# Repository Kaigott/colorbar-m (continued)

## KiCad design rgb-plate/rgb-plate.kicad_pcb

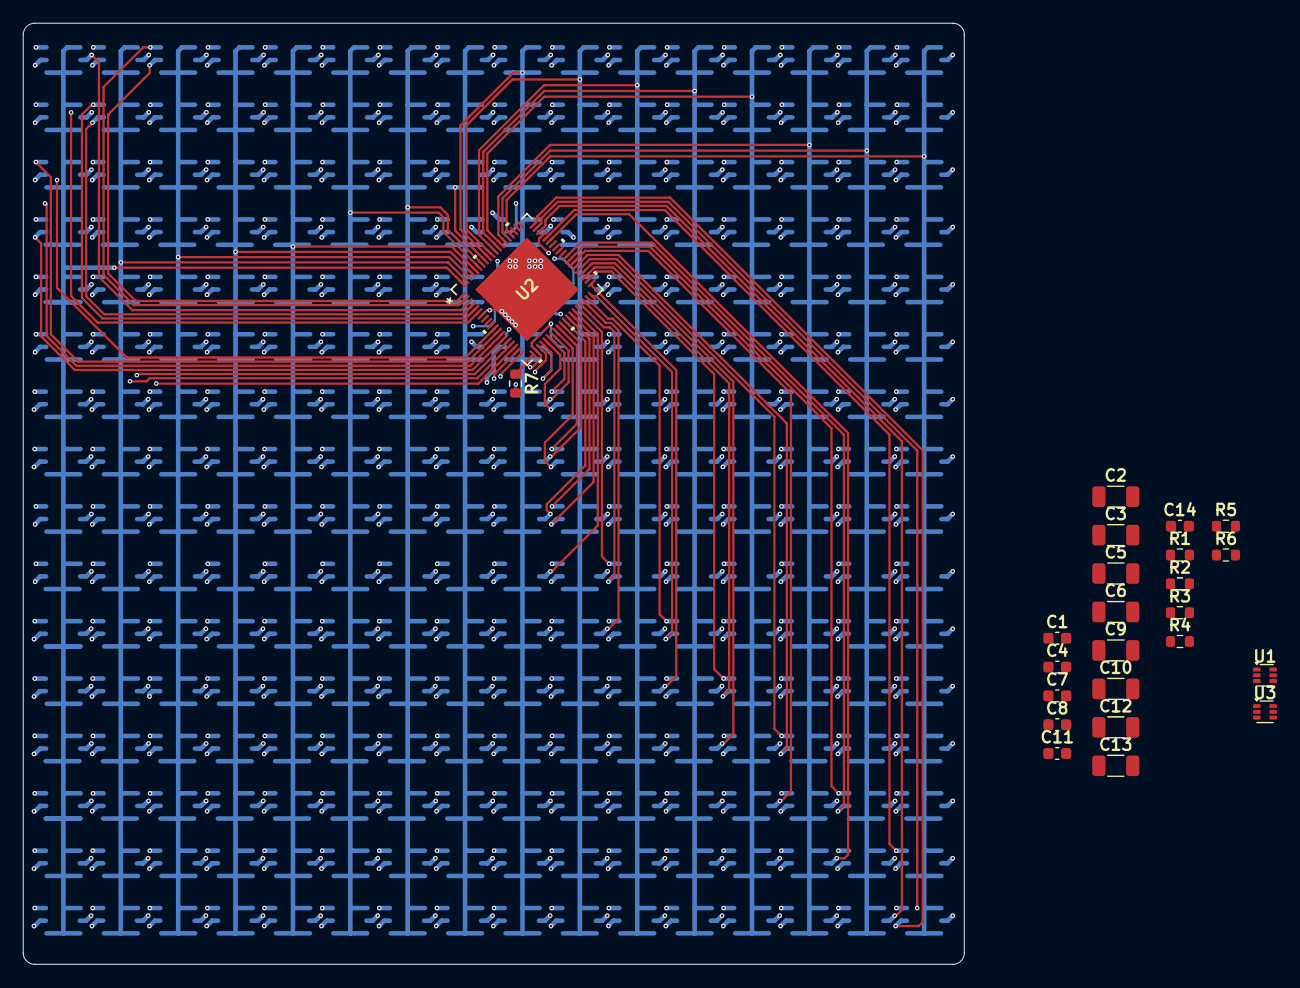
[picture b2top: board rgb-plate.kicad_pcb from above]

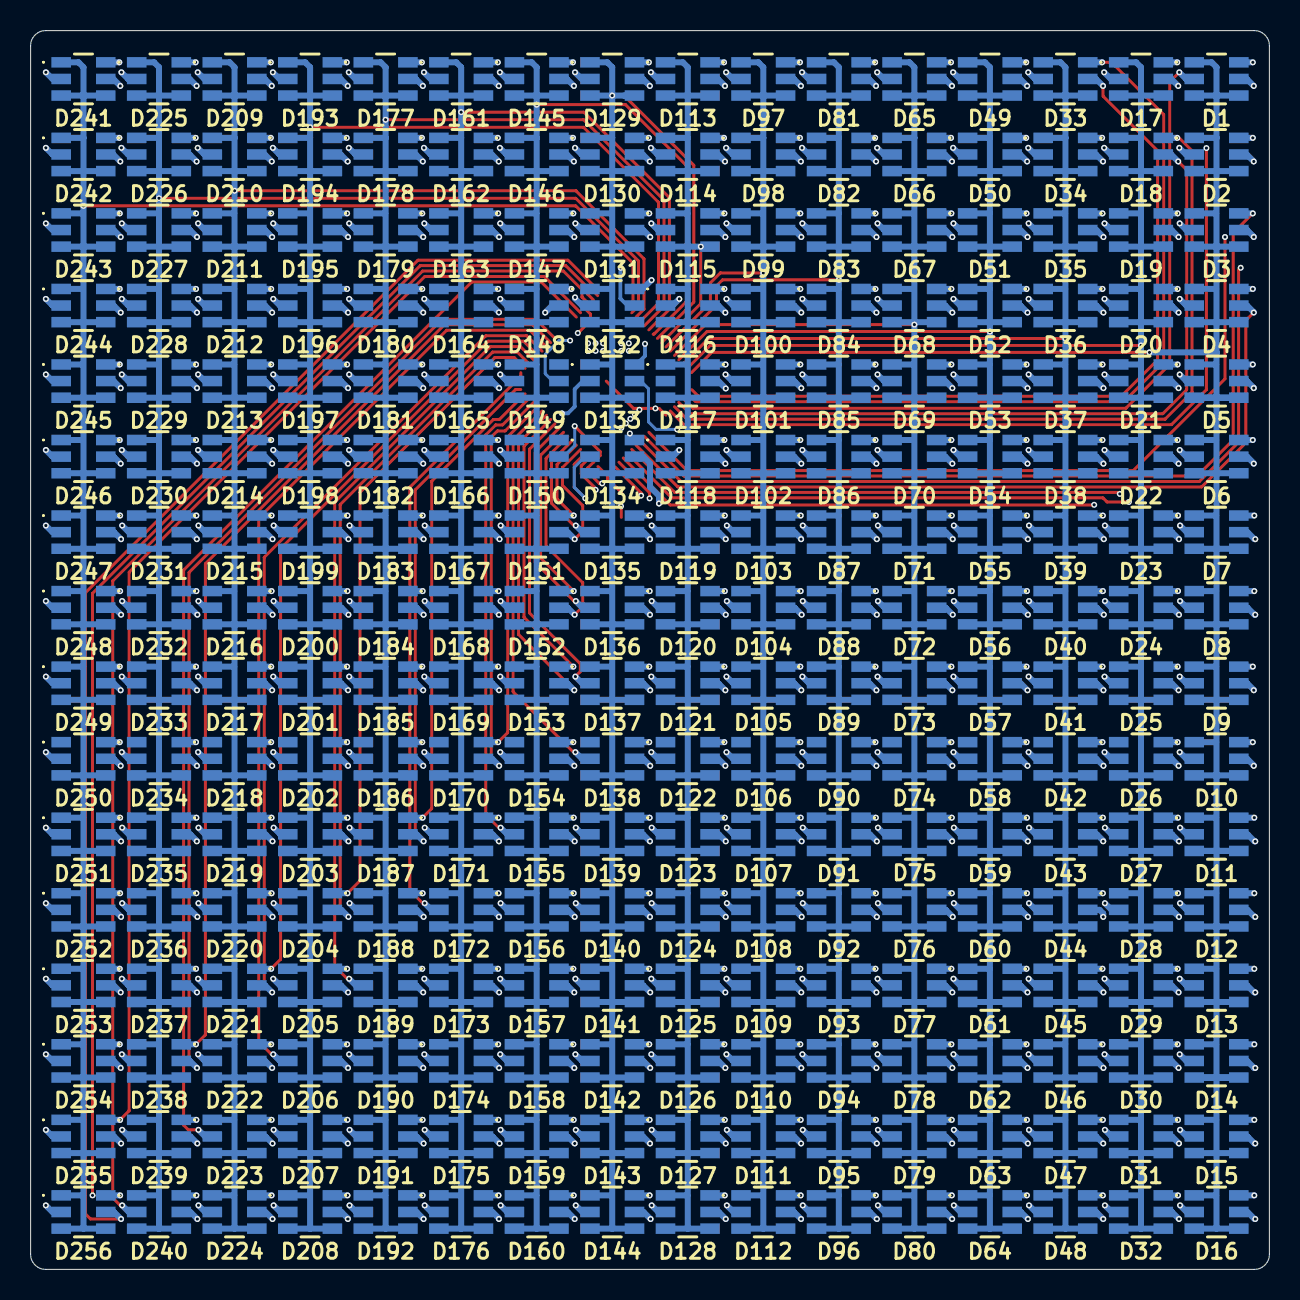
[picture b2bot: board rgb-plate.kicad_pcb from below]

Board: 4 copper layers, 82.0 x 82.0 mm, 280 parts (256 on the bottom side), 77 nets.

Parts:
C1, C4, C8, C11: 0.1uF; C_0603_1608Metric
C2, C3, C9, C10: 10uF; C_1206_3216Metric
C5, C6, C12, C13: 22uF; C_1206_3216Metric
C7, C14: 10nF; C_0603_1608Metric
D1, D2, D3, D4, D5, D6, D7, D8, D9, D10, D11, D12, D13, D14, D15, D16, D17, D18, D19, D20, D21, D22, D23, D24, D25, D26, D27, D28, D29, D30, D31, D32, D33, D34, D35, D36, D37, D38, D39, D40, D41, D42, D43, D44, D45, D46, D47, D48, D49, D50, D51, D52, D53, D54, D55, D56, D57, D58, D59, D60, D61, D62, D63, D64, D65, D66, D67, D68, D69, D70, D71, D72, D73, D74, D75, D76, D77, D78, D79, D80, D81, D82, D83, D84, D85, D86, D87, D88, D89, D90, D91, D92, D93, D94, D95, D96, D97, D98, D99, D100, D101, D102, D103, D104, D105, D106, D107, D108, D109, D110, D111, D112, D113, D114, D115, D116, D117, D118, D119, D120, D121, D122, D123, D124, D125, D126, D127, D128, D129, D130, D131, D132, D133, D134, D135, D136, D137, D138, D139, D140, D141, D142, D143, D144, D145, D146, D147, D148, D149, D150, D151, D152, D153, D154, D155, D156, D157, D158, D159, D160, D161, D162, D163, D164, D165, D166, D167, D168, D169, D170, D171, D172, D173, D174, D175, D176, D177, D178, D179, D180, D181, D182, D183, D184, D185, D186, D187, D188, D189, D190, D191, D192, D193, D194, D195, D196, D197, D198, D199, D200, D201, D202, D203, D204, D205, D206, D207, D208, D209, D210, D211, D212, D213, D214, D215, D216, D217, D218, D219, D220, D221, D222, D223, D224, D225, D226, D227, D228, D229, D230, D231, D232, D233, D234, D235, D236, D237, D238, D239, D240, D241, D242, D243, D244, D245, D246, D247, D248, D249, D250, D251, D252, D253, D254, D255, D256: LED_RGB; LRTBGVSR4U4VJW8A8BD83S4U7Z
R1, R3, R4, R6: 10k; R_0603_1608Metric
R2: 37.4k; R_0603_1608Metric
R5: 26.1k; R_0603_1608Metric
R7: R; R_0603_1608Metric
U1, U3: TPS562202; SOT-563
U2: LP5891MRRFR; VQFN76_RRF_TEX

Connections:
+2V8: C12.2, C13.2, R5.1, U2.9 (VR), U2.10 (VR)
+3V8: C5.2, C6.2, R2.1, U2.48 (VB), U2.49 (VB), U2.50 (VG), U2.51 (VG)
+12V: C2.1, C3.1, C4.1, C9.1, C10.1, C11.1, U1.1 (VIN), U3.1 (VIN)
/B0: D1.A3 (BA), D17.A3 (BA), D33.A3 (BA), D49.A3 (BA), D65.A3 (BA), D81.A3 (BA), D97.A3 (BA), D113.A3 (BA), D129.A3 (BA), D145.A3 (BA), D161.A3 (BA), D177.A3 (BA), D193.A3 (BA), D209.A3 (BA), D225.A3 (BA), D241.A3 (BA), U2.3 (B0)
/B1: D2.A3 (BA), D18.A3 (BA), D34.A3 (BA), D50.A3 (BA), D66.A3 (BA), D82.A3 (BA), D98.A3 (BA), D114.A3 (BA), D130.A3 (BA), D146.A3 (BA), D162.A3 (BA), D178.A3 (BA), D194.A3 (BA), D210.A3 (BA), D226.A3 (BA), D242.A3 (BA), U2.6 (B1)
/B2: D3.A3 (BA), D19.A3 (BA), D35.A3 (BA), D51.A3 (BA), D67.A3 (BA), D83.A3 (BA), D99.A3 (BA), D115.A3 (BA), D131.A3 (BA), D147.A3 (BA), D163.A3 (BA), D179.A3 (BA), D195.A3 (BA), D211.A3 (BA), D227.A3 (BA), D243.A3 (BA), U2.13 (B2)
/B3: D4.A3 (BA), D20.A3 (BA), D36.A3 (BA), D52.A3 (BA), D68.A3 (BA), D84.A3 (BA), D100.A3 (BA), D116.A3 (BA), D132.A3 (BA), D148.A3 (BA), D164.A3 (BA), D180.A3 (BA), D196.A3 (BA), D212.A3 (BA), D228.A3 (BA), D244.A3 (BA), U2.16 (B3)
/B4: D5.A3 (BA), D21.A3 (BA), D37.A3 (BA), D53.A3 (BA), D69.A3 (BA), D85.A3 (BA), D101.A3 (BA), D117.A3 (BA), D133.A3 (BA), D149.A3 (BA), D165.A3 (BA), D181.A3 (BA), D197.A3 (BA), D213.A3 (BA), D229.A3 (BA), D245.A3 (BA), U2.19 (B4)
/B5: D6.A3 (BA), D22.A3 (BA), D38.A3 (BA), D54.A3 (BA), D70.A3 (BA), D86.A3 (BA), D102.A3 (BA), D118.A3 (BA), D134.A3 (BA), D150.A3 (BA), D166.A3 (BA), D182.A3 (BA), D198.A3 (BA), D214.A3 (BA), D230.A3 (BA), D246.A3 (BA), U2.23 (B5)
/B6: D7.A3 (BA), D23.A3 (BA), D39.A3 (BA), D55.A3 (BA), D71.A3 (BA), D87.A3 (BA), D103.A3 (BA), D119.A3 (BA), D135.A3 (BA), D151.A3 (BA), D167.A3 (BA), D183.A3 (BA), D199.A3 (BA), D215.A3 (BA), D231.A3 (BA), D247.A3 (BA), U2.26 (B6)
/B7: D8.A3 (BA), D24.A3 (BA), D40.A3 (BA), D56.A3 (BA), D72.A3 (BA), D88.A3 (BA), D104.A3 (BA), D120.A3 (BA), D136.A3 (BA), D152.A3 (BA), D168.A3 (BA), D184.A3 (BA), D200.A3 (BA), D216.A3 (BA), D232.A3 (BA), D248.A3 (BA), U2.29 (B7)
/B8: D9.A3 (BA), D25.A3 (BA), D41.A3 (BA), D57.A3 (BA), D73.A3 (BA), D89.A3 (BA), D105.A3 (BA), D121.A3 (BA), D137.A3 (BA), D153.A3 (BA), D169.A3 (BA), D185.A3 (BA), D201.A3 (BA), D217.A3 (BA), D233.A3 (BA), D249.A3 (BA), U2.30 (B8)
/B9: D10.A3 (BA), D26.A3 (BA), D42.A3 (BA), D58.A3 (BA), D74.A3 (BA), D90.A3 (BA), D106.A3 (BA), D122.A3 (BA), D138.A3 (BA), D154.A3 (BA), D170.A3 (BA), D186.A3 (BA), D202.A3 (BA), D218.A3 (BA), D234.A3 (BA), D250.A3 (BA), U2.33 (B9)
/B10: D11.A3 (BA), D27.A3 (BA), D43.A3 (BA), D59.A3 (BA), D75.A3 (BA), D91.A3 (BA), D107.A3 (BA), D123.A3 (BA), D139.A3 (BA), D155.A3 (BA), D171.A3 (BA), D187.A3 (BA), D203.A3 (BA), D219.A3 (BA), D235.A3 (BA), D251.A3 (BA), U2.36 (B10)
/B11: D12.A3 (BA), D28.A3 (BA), D44.A3 (BA), D60.A3 (BA), D76.A3 (BA), D92.A3 (BA), D108.A3 (BA), D124.A3 (BA), D140.A3 (BA), D156.A3 (BA), D172.A3 (BA), D188.A3 (BA), D204.A3 (BA), D220.A3 (BA), D236.A3 (BA), D252.A3 (BA), U2.39 (B11)
/B12: D13.A3 (BA), D29.A3 (BA), D45.A3 (BA), D61.A3 (BA), D77.A3 (BA), D93.A3 (BA), D109.A3 (BA), D125.A3 (BA), D141.A3 (BA), D157.A3 (BA), D173.A3 (BA), D189.A3 (BA), D205.A3 (BA), D221.A3 (BA), D237.A3 (BA), D253.A3 (BA), U2.42 (B12)
/B13: D14.A3 (BA), D30.A3 (BA), D46.A3 (BA), D62.A3 (BA), D78.A3 (BA), D94.A3 (BA), D110.A3 (BA), D126.A3 (BA), D142.A3 (BA), D158.A3 (BA), D174.A3 (BA), D190.A3 (BA), D206.A3 (BA), D222.A3 (BA), D238.A3 (BA), D254.A3 (BA), U2.45 (B13)
/B14: D15.A3 (BA), D31.A3 (BA), D47.A3 (BA), D63.A3 (BA), D79.A3 (BA), D95.A3 (BA), D111.A3 (BA), D127.A3 (BA), D143.A3 (BA), D159.A3 (BA), D175.A3 (BA), D191.A3 (BA), D207.A3 (BA), D223.A3 (BA), D239.A3 (BA), D255.A3 (BA), U2.52 (B14)
/B15: D16.A3 (BA), D32.A3 (BA), D48.A3 (BA), D64.A3 (BA), D80.A3 (BA), D96.A3 (BA), D112.A3 (BA), D128.A3 (BA), D144.A3 (BA), D160.A3 (BA), D176.A3 (BA), D192.A3 (BA), D208.A3 (BA), D224.A3 (BA), D240.A3 (BA), D256.A3 (BA), U2.55 (B15)
/G0: D1.A1 (GA), D17.A1 (GA), D33.A1 (GA), D49.A1 (GA), D65.A1 (GA), D81.A1 (GA), D97.A1 (GA), D113.A1 (GA), D129.A1 (GA), D145.A1 (GA), D161.A1 (GA), D177.A1 (GA), D193.A1 (GA), D209.A1 (GA), D225.A1 (GA), D241.A1 (GA), U2.2 (G0)
/G1: D2.A1 (GA), D18.A1 (GA), D34.A1 (GA), D50.A1 (GA), D66.A1 (GA), D82.A1 (GA), D98.A1 (GA), D114.A1 (GA), D130.A1 (GA), D146.A1 (GA), D162.A1 (GA), D178.A1 (GA), D194.A1 (GA), D210.A1 (GA), D226.A1 (GA), D242.A1 (GA), U2.5 (G1)
/G2: D3.A1 (GA), D19.A1 (GA), D35.A1 (GA), D51.A1 (GA), D67.A1 (GA), D83.A1 (GA), D99.A1 (GA), D115.A1 (GA), D131.A1 (GA), D147.A1 (GA), D163.A1 (GA), D179.A1 (GA), D195.A1 (GA), D211.A1 (GA), D227.A1 (GA), D243.A1 (GA), U2.12 (G2)
/G3: D4.A1 (GA), D20.A1 (GA), D36.A1 (GA), D52.A1 (GA), D68.A1 (GA), D84.A1 (GA), D100.A1 (GA), D116.A1 (GA), D132.A1 (GA), D148.A1 (GA), D164.A1 (GA), D180.A1 (GA), D196.A1 (GA), D212.A1 (GA), D228.A1 (GA), D244.A1 (GA), U2.15 (G3)
/G4: D5.A1 (GA), D21.A1 (GA), D37.A1 (GA), D53.A1 (GA), D69.A1 (GA), D85.A1 (GA), D101.A1 (GA), D117.A1 (GA), D133.A1 (GA), D149.A1 (GA), D165.A1 (GA), D181.A1 (GA), D197.A1 (GA), D213.A1 (GA), D229.A1 (GA), D245.A1 (GA), U2.18 (G4)
/G5: D6.A1 (GA), D22.A1 (GA), D38.A1 (GA), D54.A1 (GA), D70.A1 (GA), D86.A1 (GA), D102.A1 (GA), D118.A1 (GA), D134.A1 (GA), D150.A1 (GA), D166.A1 (GA), D182.A1 (GA), D198.A1 (GA), D214.A1 (GA), D230.A1 (GA), D246.A1 (GA), U2.22 (G5)
/G6: D7.A1 (GA), D23.A1 (GA), D39.A1 (GA), D55.A1 (GA), D71.A1 (GA), D87.A1 (GA), D103.A1 (GA), D119.A1 (GA), D135.A1 (GA), D151.A1 (GA), D167.A1 (GA), D183.A1 (GA), D199.A1 (GA), D215.A1 (GA), D231.A1 (GA), D247.A1 (GA), U2.25 (G6)
/G7: D8.A1 (GA), D24.A1 (GA), D40.A1 (GA), D56.A1 (GA), D72.A1 (GA), D88.A1 (GA), D104.A1 (GA), D120.A1 (GA), D136.A1 (GA), D152.A1 (GA), D168.A1 (GA), D184.A1 (GA), D200.A1 (GA), D216.A1 (GA), D232.A1 (GA), D248.A1 (GA), U2.28 (G7)
/G8: D9.A1 (GA), D25.A1 (GA), D41.A1 (GA), D57.A1 (GA), D73.A1 (GA), D89.A1 (GA), D105.A1 (GA), D121.A1 (GA), D137.A1 (GA), D153.A1 (GA), D169.A1 (GA), D185.A1 (GA), D201.A1 (GA), D217.A1 (GA), D233.A1 (GA), D249.A1 (GA), U2.31 (G8)
/G9: D10.A1 (GA), D26.A1 (GA), D42.A1 (GA), D58.A1 (GA), D74.A1 (GA), D90.A1 (GA), D106.A1 (GA), D122.A1 (GA), D138.A1 (GA), D154.A1 (GA), D170.A1 (GA), D186.A1 (GA), D202.A1 (GA), D218.A1 (GA), D234.A1 (GA), D250.A1 (GA), U2.34 (G9)
/G10: D11.A1 (GA), D27.A1 (GA), D43.A1 (GA), D59.A1 (GA), D75.A1 (GA), D91.A1 (GA), D107.A1 (GA), D123.A1 (GA), D139.A1 (GA), D155.A1 (GA), D171.A1 (GA), D187.A1 (GA), D203.A1 (GA), D219.A1 (GA), D235.A1 (GA), D251.A1 (GA), U2.37 (G10)
/G11: D12.A1 (GA), D28.A1 (GA), D44.A1 (GA), D60.A1 (GA), D76.A1 (GA), D92.A1 (GA), D108.A1 (GA), D124.A1 (GA), D140.A1 (GA), D156.A1 (GA), D172.A1 (GA), D188.A1 (GA), D204.A1 (GA), D220.A1 (GA), D236.A1 (GA), D252.A1 (GA), U2.40 (G11)
/G12: D13.A1 (GA), D29.A1 (GA), D45.A1 (GA), D61.A1 (GA), D77.A1 (GA), D93.A1 (GA), D109.A1 (GA), D125.A1 (GA), D141.A1 (GA), D157.A1 (GA), D173.A1 (GA), D189.A1 (GA), D205.A1 (GA), D221.A1 (GA), D237.A1 (GA), D253.A1 (GA), U2.43 (G12)
/G13: D14.A1 (GA), D30.A1 (GA), D46.A1 (GA), D62.A1 (GA), D78.A1 (GA), D94.A1 (GA), D110.A1 (GA), D126.A1 (GA), D142.A1 (GA), D158.A1 (GA), D174.A1 (GA), D190.A1 (GA), D206.A1 (GA), D222.A1 (GA), D238.A1 (GA), D254.A1 (GA), U2.46 (G13)
/G14: D15.A1 (GA), D31.A1 (GA), D47.A1 (GA), D63.A1 (GA), D79.A1 (GA), D95.A1 (GA), D111.A1 (GA), D127.A1 (GA), D143.A1 (GA), D159.A1 (GA), D175.A1 (GA), D191.A1 (GA), D207.A1 (GA), D223.A1 (GA), D239.A1 (GA), D255.A1 (GA), U2.53 (G14)
/G15: D16.A1 (GA), D32.A1 (GA), D48.A1 (GA), D64.A1 (GA), D80.A1 (GA), D96.A1 (GA), D112.A1 (GA), D128.A1 (GA), D144.A1 (GA), D160.A1 (GA), D176.A1 (GA), D192.A1 (GA), D208.A1 (GA), D224.A1 (GA), D240.A1 (GA), D256.A1 (GA), U2.56 (G15)
/LINE0: D1.C1 (GK), D1.C2 (RK), D1.C3 (BK), D2.C1 (GK), D2.C2 (RK), D2.C3 (BK), D3.C1 (GK), D3.C2 (RK), D3.C3 (BK), D4.C1 (GK), D4.C2 (RK), D4.C3 (BK), D5.C1 (GK), D5.C2 (RK), D5.C3 (BK), D6.C1 (GK), D6.C2 (RK), D6.C3 (BK), D7.C1 (GK), D7.C2 (RK), D7.C3 (BK), D8.C1 (GK), D8.C2 (RK), D8.C3 (BK), D9.C1 (GK), D9.C2 (RK), D9.C3 (BK), D10.C1 (GK), D10.C2 (RK), D10.C3 (BK), D11.C1 (GK), D11.C2 (RK), D11.C3 (BK), D12.C1 (GK), D12.C2 (RK), D12.C3 (BK), D13.C1 (GK), D13.C2 (RK), D13.C3 (BK), D14.C1 (GK), D14.C2 (RK), D14.C3 (BK), D15.C1 (GK), D15.C2 (RK), D15.C3 (BK), D16.C1 (GK), D16.C2 (RK), D16.C3 (BK), U2.76 (LINE0)
/LINE1: D17.C1 (GK), D17.C2 (RK), D17.C3 (BK), D18.C1 (GK), D18.C2 (RK), D18.C3 (BK), D19.C1 (GK), D19.C2 (RK), D19.C3 (BK), D20.C1 (GK), D20.C2 (RK), D20.C3 (BK), D21.C1 (GK), D21.C2 (RK), D21.C3 (BK), D22.C1 (GK), D22.C2 (RK), D22.C3 (BK), D23.C1 (GK), D23.C2 (RK), D23.C3 (BK), D24.C1 (GK), D24.C2 (RK), D24.C3 (BK), D25.C1 (GK), D25.C2 (RK), D25.C3 (BK), D26.C1 (GK), D26.C2 (RK), D26.C3 (BK), D27.C1 (GK), D27.C2 (RK), D27.C3 (BK), D28.C1 (GK), D28.C2 (RK), D28.C3 (BK), D29.C1 (GK), D29.C2 (RK), D29.C3 (BK), D30.C1 (GK), D30.C2 (RK), D30.C3 (BK), D31.C1 (GK), D31.C2 (RK), D31.C3 (BK), D32.C1 (GK), D32.C2 (RK), D32.C3 (BK), U2.75 (LINE1)
/LINE2: D33.C1 (GK), D33.C2 (RK), D33.C3 (BK), D34.C1 (GK), D34.C2 (RK), D34.C3 (BK), D35.C1 (GK), D35.C2 (RK), D35.C3 (BK), D36.C1 (GK), D36.C2 (RK), D36.C3 (BK), D37.C1 (GK), D37.C2 (RK), D37.C3 (BK), D38.C1 (GK), D38.C2 (RK), D38.C3 (BK), D39.C1 (GK), D39.C2 (RK), D39.C3 (BK), D40.C1 (GK), D40.C2 (RK), D40.C3 (BK), D41.C1 (GK), D41.C2 (RK), D41.C3 (BK), D42.C1 (GK), D42.C2 (RK), D42.C3 (BK), D43.C1 (GK), D43.C2 (RK), D43.C3 (BK), D44.C1 (GK), D44.C2 (RK), D44.C3 (BK), D45.C1 (GK), D45.C2 (RK), D45.C3 (BK), D46.C1 (GK), D46.C2 (RK), D46.C3 (BK), D47.C1 (GK), D47.C2 (RK), D47.C3 (BK), D48.C1 (GK), D48.C2 (RK), D48.C3 (BK), U2.74 (LINE2)
/LINE3: D49.C1 (GK), D49.C2 (RK), D49.C3 (BK), D50.C1 (GK), D50.C2 (RK), D50.C3 (BK), D51.C1 (GK), D51.C2 (RK), D51.C3 (BK), D52.C1 (GK), D52.C2 (RK), D52.C3 (BK), D53.C1 (GK), D53.C2 (RK), D53.C3 (BK), D54.C1 (GK), D54.C2 (RK), D54.C3 (BK), D55.C1 (GK), D55.C2 (RK), D55.C3 (BK), D56.C1 (GK), D56.C2 (RK), D56.C3 (BK), D57.C1 (GK), D57.C2 (RK), D57.C3 (BK), D58.C1 (GK), D58.C2 (RK), D58.C3 (BK), D59.C1 (GK), D59.C2 (RK), D59.C3 (BK), D60.C1 (GK), D60.C2 (RK), D60.C3 (BK), D61.C1 (GK), D61.C2 (RK), D61.C3 (BK), D62.C1 (GK), D62.C2 (RK), D62.C3 (BK), D63.C1 (GK), D63.C2 (RK), D63.C3 (BK), D64.C1 (GK), D64.C2 (RK), D64.C3 (BK), U2.73 (LINE3)
/LINE4: D65.C1 (GK), D65.C2 (RK), D65.C3 (BK), D66.C1 (GK), D66.C2 (RK), D66.C3 (BK), D67.C1 (GK), D67.C2 (RK), D67.C3 (BK), D68.C1 (GK), D68.C2 (RK), D68.C3 (BK), D69.C1 (GK), D69.C2 (RK), D69.C3 (BK), D70.C1 (GK), D70.C2 (RK), D70.C3 (BK), D71.C1 (GK), D71.C2 (RK), D71.C3 (BK), D72.C1 (GK), D72.C2 (RK), D72.C3 (BK), D73.C1 (GK), D73.C2 (RK), D73.C3 (BK), D74.C1 (GK), D74.C2 (RK), D74.C3 (BK), D75.C1 (GK), D75.C2 (RK), D75.C3 (BK), D76.C1 (GK), D76.C2 (RK), D76.C3 (BK), D77.C1 (GK), D77.C2 (RK), D77.C3 (BK), D78.C1 (GK), D78.C2 (RK), D78.C3 (BK), D79.C1 (GK), D79.C2 (RK), D79.C3 (BK), D80.C1 (GK), D80.C2 (RK), D80.C3 (BK), U2.72 (LINE4)
/LINE5: D81.C1 (GK), D81.C2 (RK), D81.C3 (BK), D82.C1 (GK), D82.C2 (RK), D82.C3 (BK), D83.C1 (GK), D83.C2 (RK), D83.C3 (BK), D84.C1 (GK), D84.C2 (RK), D84.C3 (BK), D85.C1 (GK), D85.C2 (RK), D85.C3 (BK), D86.C1 (GK), D86.C2 (RK), D86.C3 (BK), D87.C1 (GK), D87.C2 (RK), D87.C3 (BK), D88.C1 (GK), D88.C2 (RK), D88.C3 (BK), D89.C1 (GK), D89.C2 (RK), D89.C3 (BK), D90.C1 (GK), D90.C2 (RK), D90.C3 (BK), D91.C1 (GK), D91.C2 (RK), D91.C3 (BK), D92.C1 (GK), D92.C2 (RK), D92.C3 (BK), D93.C1 (GK), D93.C2 (RK), D93.C3 (BK), D94.C1 (GK), D94.C2 (RK), D94.C3 (BK), D95.C1 (GK), D95.C2 (RK), D95.C3 (BK), D96.C1 (GK), D96.C2 (RK), D96.C3 (BK), U2.71 (LINE5)
/LINE6: D97.C1 (GK), D97.C2 (RK), D97.C3 (BK), D98.C1 (GK), D98.C2 (RK), D98.C3 (BK), D99.C1 (GK), D99.C2 (RK), D99.C3 (BK), D100.C1 (GK), D100.C2 (RK), D100.C3 (BK), D101.C1 (GK), D101.C2 (RK), D101.C3 (BK), D102.C1 (GK), D102.C2 (RK), D102.C3 (BK), D103.C1 (GK), D103.C2 (RK), D103.C3 (BK), D104.C1 (GK), D104.C2 (RK), D104.C3 (BK), D105.C1 (GK), D105.C2 (RK), D105.C3 (BK), D106.C1 (GK), D106.C2 (RK), D106.C3 (BK), D107.C1 (GK), D107.C2 (RK), D107.C3 (BK), D108.C1 (GK), D108.C2 (RK), D108.C3 (BK), D109.C1 (GK), D109.C2 (RK), D109.C3 (BK), D110.C1 (GK), D110.C2 (RK), D110.C3 (BK), D111.C1 (GK), D111.C2 (RK), D111.C3 (BK), D112.C1 (GK), D112.C2 (RK), D112.C3 (BK), U2.70 (LINE6)
/LINE7: D113.C1 (GK), D113.C2 (RK), D113.C3 (BK), D114.C1 (GK), D114.C2 (RK), D114.C3 (BK), D115.C1 (GK), D115.C2 (RK), D115.C3 (BK), D116.C1 (GK), D116.C2 (RK), D116.C3 (BK), D117.C1 (GK), D117.C2 (RK), D117.C3 (BK), D118.C1 (GK), D118.C2 (RK), D118.C3 (BK), D119.C1 (GK), D119.C2 (RK), D119.C3 (BK), D120.C1 (GK), D120.C2 (RK), D120.C3 (BK), D121.C1 (GK), D121.C2 (RK), D121.C3 (BK), D122.C1 (GK), D122.C2 (RK), D122.C3 (BK), D123.C1 (GK), D123.C2 (RK), D123.C3 (BK), D124.C1 (GK), D124.C2 (RK), D124.C3 (BK), D125.C1 (GK), D125.C2 (RK), D125.C3 (BK), D126.C1 (GK), D126.C2 (RK), D126.C3 (BK), D127.C1 (GK), D127.C2 (RK), D127.C3 (BK), D128.C1 (GK), D128.C2 (RK), D128.C3 (BK), U2.69 (LINE7)
/LINE8: D129.C1 (GK), D129.C2 (RK), D129.C3 (BK), D130.C1 (GK), D130.C2 (RK), D130.C3 (BK), D131.C1 (GK), D131.C2 (RK), D131.C3 (BK), D132.C1 (GK), D132.C2 (RK), D132.C3 (BK), D133.C1 (GK), D133.C2 (RK), D133.C3 (BK), D134.C1 (GK), D134.C2 (RK), D134.C3 (BK), D135.C1 (GK), D135.C2 (RK), D135.C3 (BK), D136.C1 (GK), D136.C2 (RK), D136.C3 (BK), D137.C1 (GK), D137.C2 (RK), D137.C3 (BK), D138.C1 (GK), D138.C2 (RK), D138.C3 (BK), D139.C1 (GK), D139.C2 (RK), D139.C3 (BK), D140.C1 (GK), D140.C2 (RK), D140.C3 (BK), D141.C1 (GK), D141.C2 (RK), D141.C3 (BK), D142.C1 (GK), D142.C2 (RK), D142.C3 (BK), D143.C1 (GK), D143.C2 (RK), D143.C3 (BK), D144.C1 (GK), D144.C2 (RK), D144.C3 (BK), U2.68 (LINE8)
/LINE9: D145.C1 (GK), D145.C2 (RK), D145.C3 (BK), D146.C1 (GK), D146.C2 (RK), D146.C3 (BK), D147.C1 (GK), D147.C2 (RK), D147.C3 (BK), D148.C1 (GK), D148.C2 (RK), D148.C3 (BK), D149.C1 (GK), D149.C2 (RK), D149.C3 (BK), D150.C1 (GK), D150.C2 (RK), D150.C3 (BK), D151.C1 (GK), D151.C2 (RK), D151.C3 (BK), D152.C1 (GK), D152.C2 (RK), D152.C3 (BK), D153.C1 (GK), D153.C2 (RK), D153.C3 (BK), D154.C1 (GK), D154.C2 (RK), D154.C3 (BK), D155.C1 (GK), D155.C2 (RK), D155.C3 (BK), D156.C1 (GK), D156.C2 (RK), D156.C3 (BK), D157.C1 (GK), D157.C2 (RK), D157.C3 (BK), D158.C1 (GK), D158.C2 (RK), D158.C3 (BK), D159.C1 (GK), D159.C2 (RK), D159.C3 (BK), D160.C1 (GK), D160.C2 (RK), D160.C3 (BK), U2.67 (LINE9)
/LINE10: D161.C1 (GK), D161.C2 (RK), D161.C3 (BK), D162.C1 (GK), D162.C2 (RK), D162.C3 (BK), D163.C1 (GK), D163.C2 (RK), D163.C3 (BK), D164.C1 (GK), D164.C2 (RK), D164.C3 (BK), D165.C1 (GK), D165.C2 (RK), D165.C3 (BK), D166.C1 (GK), D166.C2 (RK), D166.C3 (BK), D167.C1 (GK), D167.C2 (RK), D167.C3 (BK), D168.C1 (GK), D168.C2 (RK), D168.C3 (BK), D169.C1 (GK), D169.C2 (RK), D169.C3 (BK), D170.C1 (GK), D170.C2 (RK), D170.C3 (BK), D171.C1 (GK), D171.C2 (RK), D171.C3 (BK), D172.C1 (GK), D172.C2 (RK), D172.C3 (BK), D173.C1 (GK), D173.C2 (RK), D173.C3 (BK), D174.C1 (GK), D174.C2 (RK), D174.C3 (BK), D175.C1 (GK), D175.C2 (RK), D175.C3 (BK), D176.C1 (GK), D176.C2 (RK), D176.C3 (BK), U2.66 (LINE10)
/LINE11: D177.C1 (GK), D177.C2 (RK), D177.C3 (BK), D178.C1 (GK), D178.C2 (RK), D178.C3 (BK), D179.C1 (GK), D179.C2 (RK), D179.C3 (BK), D180.C1 (GK), D180.C2 (RK), D180.C3 (BK), D181.C1 (GK), D181.C2 (RK), D181.C3 (BK), D182.C1 (GK), D182.C2 (RK), D182.C3 (BK), D183.C1 (GK), D183.C2 (RK), D183.C3 (BK), D184.C1 (GK), D184.C2 (RK), D184.C3 (BK), D185.C1 (GK), D185.C2 (RK), D185.C3 (BK), D186.C1 (GK), D186.C2 (RK), D186.C3 (BK), D187.C1 (GK), D187.C2 (RK), D187.C3 (BK), D188.C1 (GK), D188.C2 (RK), D188.C3 (BK), D189.C1 (GK), D189.C2 (RK), D189.C3 (BK), D190.C1 (GK), D190.C2 (RK), D190.C3 (BK), D191.C1 (GK), D191.C2 (RK), D191.C3 (BK), D192.C1 (GK), D192.C2 (RK), D192.C3 (BK), U2.65 (LINE11)
/LINE12: D193.C1 (GK), D193.C2 (RK), D193.C3 (BK), D194.C1 (GK), D194.C2 (RK), D194.C3 (BK), D195.C1 (GK), D195.C2 (RK), D195.C3 (BK), D196.C1 (GK), D196.C2 (RK), D196.C3 (BK), D197.C1 (GK), D197.C2 (RK), D197.C3 (BK), D198.C1 (GK), D198.C2 (RK), D198.C3 (BK), D199.C1 (GK), D199.C2 (RK), D199.C3 (BK), D200.C1 (GK), D200.C2 (RK), D200.C3 (BK), D201.C1 (GK), D201.C2 (RK), D201.C3 (BK), D202.C1 (GK), D202.C2 (RK), D202.C3 (BK), D203.C1 (GK), D203.C2 (RK), D203.C3 (BK), D204.C1 (GK), D204.C2 (RK), D204.C3 (BK), D205.C1 (GK), D205.C2 (RK), D205.C3 (BK), D206.C1 (GK), D206.C2 (RK), D206.C3 (BK), D207.C1 (GK), D207.C2 (RK), D207.C3 (BK), D208.C1 (GK), D208.C2 (RK), D208.C3 (BK), U2.64 (LINE12)
/LINE13: D209.C1 (GK), D209.C2 (RK), D209.C3 (BK), D210.C1 (GK), D210.C2 (RK), D210.C3 (BK), D211.C1 (GK), D211.C2 (RK), D211.C3 (BK), D212.C1 (GK), D212.C2 (RK), D212.C3 (BK), D213.C1 (GK), D213.C2 (RK), D213.C3 (BK), D214.C1 (GK), D214.C2 (RK), D214.C3 (BK), D215.C1 (GK), D215.C2 (RK), D215.C3 (BK), D216.C1 (GK), D216.C2 (RK), D216.C3 (BK), D217.C1 (GK), D217.C2 (RK), D217.C3 (BK), D218.C1 (GK), D218.C2 (RK), D218.C3 (BK), D219.C1 (GK), D219.C2 (RK), D219.C3 (BK), D220.C1 (GK), D220.C2 (RK), D220.C3 (BK), D221.C1 (GK), D221.C2 (RK), D221.C3 (BK), D222.C1 (GK), D222.C2 (RK), D222.C3 (BK), D223.C1 (GK), D223.C2 (RK), D223.C3 (BK), D224.C1 (GK), D224.C2 (RK), D224.C3 (BK), U2.63 (LINE13)
/LINE14: D225.C1 (GK), D225.C2 (RK), D225.C3 (BK), D226.C1 (GK), D226.C2 (RK), D226.C3 (BK), D227.C1 (GK), D227.C2 (RK), D227.C3 (BK), D228.C1 (GK), D228.C2 (RK), D228.C3 (BK), D229.C1 (GK), D229.C2 (RK), D229.C3 (BK), D230.C1 (GK), D230.C2 (RK), D230.C3 (BK), D231.C1 (GK), D231.C2 (RK), D231.C3 (BK), D232.C1 (GK), D232.C2 (RK), D232.C3 (BK), D233.C1 (GK), D233.C2 (RK), D233.C3 (BK), D234.C1 (GK), D234.C2 (RK), D234.C3 (BK), D235.C1 (GK), D235.C2 (RK), D235.C3 (BK), D236.C1 (GK), D236.C2 (RK), D236.C3 (BK), D237.C1 (GK), D237.C2 (RK), D237.C3 (BK), D238.C1 (GK), D238.C2 (RK), D238.C3 (BK), D239.C1 (GK), D239.C2 (RK), D239.C3 (BK), D240.C1 (GK), D240.C2 (RK), D240.C3 (BK), U2.62 (LINE14)
/LINE15: D241.C1 (GK), D241.C2 (RK), D241.C3 (BK), D242.C1 (GK), D242.C2 (RK), D242.C3 (BK), D243.C1 (GK), D243.C2 (RK), D243.C3 (BK), D244.C1 (GK), D244.C2 (RK), D244.C3 (BK), D245.C1 (GK), D245.C2 (RK), D245.C3 (BK), D246.C1 (GK), D246.C2 (RK), D246.C3 (BK), D247.C1 (GK), D247.C2 (RK), D247.C3 (BK), D248.C1 (GK), D248.C2 (RK), D248.C3 (BK), D249.C1 (GK), D249.C2 (RK), D249.C3 (BK), D250.C1 (GK), D250.C2 (RK), D250.C3 (BK), D251.C1 (GK), D251.C2 (RK), D251.C3 (BK), D252.C1 (GK), D252.C2 (RK), D252.C3 (BK), D253.C1 (GK), D253.C2 (RK), D253.C3 (BK), D254.C1 (GK), D254.C2 (RK), D254.C3 (BK), D255.C1 (GK), D255.C2 (RK), D255.C3 (BK), D256.C1 (GK), D256.C2 (RK), D256.C3 (BK), U2.61 (LINE15)
/R0: D1.A2 (RA), D17.A2 (RA), D33.A2 (RA), D49.A2 (RA), D65.A2 (RA), D81.A2 (RA), D97.A2 (RA), D113.A2 (RA), D129.A2 (RA), D145.A2 (RA), D161.A2 (RA), D177.A2 (RA), D193.A2 (RA), D209.A2 (RA), D225.A2 (RA), D241.A2 (RA), U2.1 (R0)
/R1: D2.A2 (RA), D18.A2 (RA), D34.A2 (RA), D50.A2 (RA), D66.A2 (RA), D82.A2 (RA), D98.A2 (RA), D114.A2 (RA), D130.A2 (RA), D146.A2 (RA), D162.A2 (RA), D178.A2 (RA), D194.A2 (RA), D210.A2 (RA), D226.A2 (RA), D242.A2 (RA), U2.4 (R1)
/R2: D3.A2 (RA), D19.A2 (RA), D35.A2 (RA), D51.A2 (RA), D67.A2 (RA), D83.A2 (RA), D99.A2 (RA), D115.A2 (RA), D131.A2 (RA), D147.A2 (RA), D163.A2 (RA), D179.A2 (RA), D195.A2 (RA), D211.A2 (RA), D227.A2 (RA), D243.A2 (RA), U2.11 (R2)
/R3: D4.A2 (RA), D20.A2 (RA), D36.A2 (RA), D52.A2 (RA), D68.A2 (RA), D84.A2 (RA), D100.A2 (RA), D116.A2 (RA), D132.A2 (RA), D148.A2 (RA), D164.A2 (RA), D180.A2 (RA), D196.A2 (RA), D212.A2 (RA), D228.A2 (RA), D244.A2 (RA), U2.14 (R3)
/R4: D5.A2 (RA), D21.A2 (RA), D37.A2 (RA), D53.A2 (RA), D69.A2 (RA), D85.A2 (RA), D101.A2 (RA), D117.A2 (RA), D133.A2 (RA), D149.A2 (RA), D165.A2 (RA), D181.A2 (RA), D197.A2 (RA), D213.A2 (RA), D229.A2 (RA), D245.A2 (RA), U2.17 (R4)
/R5: D6.A2 (RA), D22.A2 (RA), D38.A2 (RA), D54.A2 (RA), D70.A2 (RA), D86.A2 (RA), D102.A2 (RA), D118.A2 (RA), D134.A2 (RA), D150.A2 (RA), D166.A2 (RA), D182.A2 (RA), D198.A2 (RA), D214.A2 (RA), D230.A2 (RA), D246.A2 (RA), U2.21 (R5)
/R6: D7.A2 (RA), D23.A2 (RA), D39.A2 (RA), D55.A2 (RA), D71.A2 (RA), D87.A2 (RA), D103.A2 (RA), D119.A2 (RA), D135.A2 (RA), D151.A2 (RA), D167.A2 (RA), D183.A2 (RA), D199.A2 (RA), D215.A2 (RA), D231.A2 (RA), D247.A2 (RA), U2.24 (R6)
/R7: D8.A2 (RA), D24.A2 (RA), D40.A2 (RA), D56.A2 (RA), D72.A2 (RA), D88.A2 (RA), D104.A2 (RA), D120.A2 (RA), D136.A2 (RA), D152.A2 (RA), D168.A2 (RA), D184.A2 (RA), D200.A2 (RA), D216.A2 (RA), D232.A2 (RA), D248.A2 (RA), U2.27 (R7)
/R8: D9.A2 (RA), D25.A2 (RA), D41.A2 (RA), D57.A2 (RA), D73.A2 (RA), D89.A2 (RA), D105.A2 (RA), D121.A2 (RA), D137.A2 (RA), D153.A2 (RA), D169.A2 (RA), D185.A2 (RA), D201.A2 (RA), D217.A2 (RA), D233.A2 (RA), D249.A2 (RA), U2.32 (R8)
/R9: D10.A2 (RA), D26.A2 (RA), D42.A2 (RA), D58.A2 (RA), D74.A2 (RA), D90.A2 (RA), D106.A2 (RA), D122.A2 (RA), D138.A2 (RA), D154.A2 (RA), D170.A2 (RA), D186.A2 (RA), D202.A2 (RA), D218.A2 (RA), D234.A2 (RA), D250.A2 (RA), U2.35 (R9)
/R10: D11.A2 (RA), D27.A2 (RA), D43.A2 (RA), D59.A2 (RA), D75.A2 (RA), D91.A2 (RA), D107.A2 (RA), D123.A2 (RA), D139.A2 (RA), D155.A2 (RA), D171.A2 (RA), D187.A2 (RA), D203.A2 (RA), D219.A2 (RA), D235.A2 (RA), D251.A2 (RA), U2.38 (R10)
/R11: D12.A2 (RA), D28.A2 (RA), D44.A2 (RA), D60.A2 (RA), D76.A2 (RA), D92.A2 (RA), D108.A2 (RA), D124.A2 (RA), D140.A2 (RA), D156.A2 (RA), D172.A2 (RA), D188.A2 (RA), D204.A2 (RA), D220.A2 (RA), D236.A2 (RA), D252.A2 (RA), U2.41 (R11)
/R12: D13.A2 (RA), D29.A2 (RA), D45.A2 (RA), D61.A2 (RA), D77.A2 (RA), D93.A2 (RA), D109.A2 (RA), D125.A2 (RA), D141.A2 (RA), D157.A2 (RA), D173.A2 (RA), D189.A2 (RA), D205.A2 (RA), D221.A2 (RA), D237.A2 (RA), D253.A2 (RA), U2.44 (R12)
/R13: D14.A2 (RA), D30.A2 (RA), D46.A2 (RA), D62.A2 (RA), D78.A2 (RA), D94.A2 (RA), D110.A2 (RA), D126.A2 (RA), D142.A2 (RA), D158.A2 (RA), D174.A2 (RA), D190.A2 (RA), D206.A2 (RA), D222.A2 (RA), D238.A2 (RA), D254.A2 (RA), U2.47 (R13)
/R14: D15.A2 (RA), D31.A2 (RA), D47.A2 (RA), D63.A2 (RA), D79.A2 (RA), D95.A2 (RA), D111.A2 (RA), D127.A2 (RA), D143.A2 (RA), D159.A2 (RA), D175.A2 (RA), D191.A2 (RA), D207.A2 (RA), D223.A2 (RA), D239.A2 (RA), D255.A2 (RA), U2.54 (R14)
/R15: D16.A2 (RA), D32.A2 (RA), D48.A2 (RA), D64.A2 (RA), D80.A2 (RA), D96.A2 (RA), D112.A2 (RA), D128.A2 (RA), D144.A2 (RA), D160.A2 (RA), D176.A2 (RA), D192.A2 (RA), D208.A2 (RA), D224.A2 (RA), D240.A2 (RA), D256.A2 (RA), U2.57 (R15)
GND: C2.2, C3.2, C4.2, C5.1, C6.1, C7.1, C9.2, C10.2, C11.2, C12.1, C13.1, C14.1, R3.2, R6.2, R7.2, U1.3 (GND), U2.7 (GND), U2.77 (EPAD), U3.3 (GND)
unnamed: R1.2, U1.5 (EN)
unnamed: C1.1, U1.2 (SW)
unnamed: C1.2, U1.4 (VBST)
unnamed: C7.2, R2.2, R3.1, U1.6 (VFB)
unnamed: R7.1, U2.20 (IREF)
unnamed: R4.2, U3.5 (EN)
unnamed: C8.1, U3.2 (SW)
unnamed: C8.2, U3.4 (VBST)
unnamed: C14.2, R5.2, R6.1, U3.6 (VFB)

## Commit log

2026-02-05 initial commit; create project file and schematic sheets
2026-02-05 added additional sheets and leds with matrix driver and first regulator
2026-02-07 added 3 regulators for power stage
2026-02-08 added regulators and components
2026-02-11 initial layout on single board, may need to split up
2026-02-12 update complete architecture to allow for improved routing scheme - separate boards for led plate and driver. adjusted matrix board to only hold leds and connectors and thermistors, created new board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
2026-02-12 laid out proper schematic and connector interface for driver, added new conn libs, todo add correct inductors
2026-02-12 added 3v3 regulator again and added footprints to layout
2026-02-19 added gerbers and finalized v1.0
2026-02-20 finished flipping ribbon connectors, drc pass, export gerbers, drill files, and pick and place files
2026-02-21 updated cpl file for jlcpcb compatibility
2026-02-21 changed to through hole connectors for matrix drive unit and updated schematic to reflect thermistors and reserved pin
